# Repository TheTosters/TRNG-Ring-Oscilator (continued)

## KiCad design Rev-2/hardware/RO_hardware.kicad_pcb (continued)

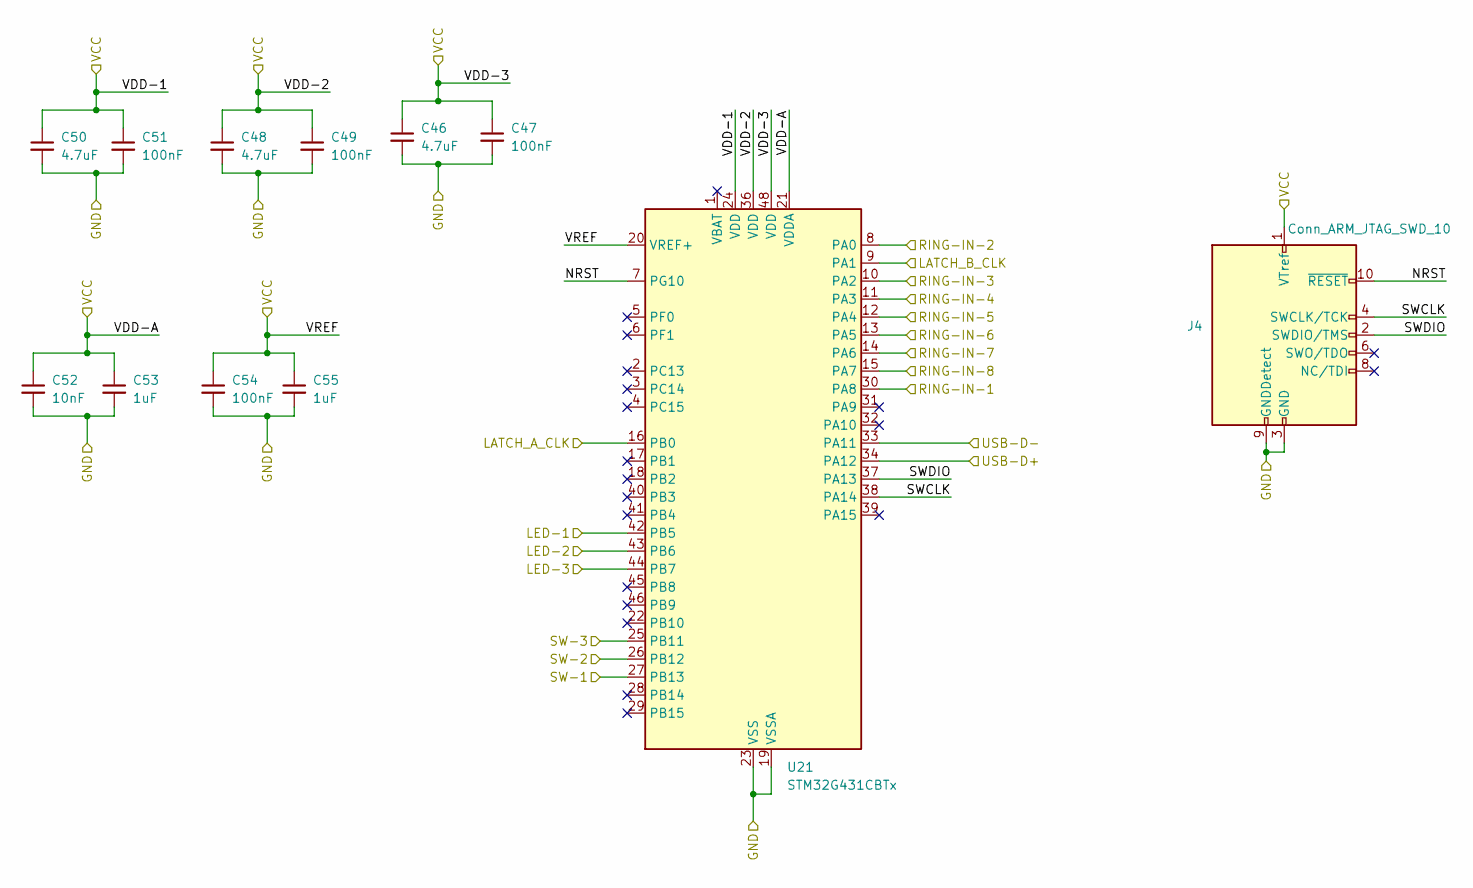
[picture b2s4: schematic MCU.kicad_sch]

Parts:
C46, C48, C50: 4.7uF; C_1206_3216Metric
C47, C49, C51, C54: 100nF; C_1206_3216Metric
C52: 10nF; C_1206_3216Metric
C53, C55: 1uF; C_1206_3216Metric
J4: Conn_ARM_JTAG_SWD_10; Tag-Connect_TC2050-IDC-NL_2x05_P1.27mm_Vertical
U21: STM32G431CBTx; LQFP-48_7x7mm_P0.5mm

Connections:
/CLK_A: U21.16 (PB0); also elsewhere on the board
/CLK_B: U21.9 (PA1); also elsewhere on the board
/D+: U21.34 (PA12); also elsewhere on the board
/D-: U21.33 (PA11); also elsewhere on the board
/MCU/LED-1: U21.42 (PB5); also elsewhere on the board
/MCU/LED-2: U21.43 (PB6); also elsewhere on the board
/MCU/LED-3: U21.44 (PB7); also elsewhere on the board
/MCU/NRST: J4.10 (~RESET), U21.7 (PG10)
/MCU/SW-1: U21.27 (PB13); also elsewhere on the board
/MCU/SW-2: U21.26 (PB12); also elsewhere on the board
/MCU/SW-3: U21.25 (PB11); also elsewhere on the board
/MCU/SWCLK: J4.4 (SWCLK/TCK), U21.38 (PA14)
/MCU/SWDIO: J4.2 (SWDIO/TMS), U21.37 (PA13)
/Q1: U21.12 (PA4); also elsewhere on the board
/Q2: U21.13 (PA5); also elsewhere on the board
/Q3: U21.15 (PA7); also elsewhere on the board
/Q4: U21.14 (PA6); also elsewhere on the board
/TQ1: U21.30 (PA8); also elsewhere on the board
/TQ2: U21.8 (PA0); also elsewhere on the board
/TQ3: U21.11 (PA3); also elsewhere on the board
/TQ4: U21.10 (PA2); also elsewhere on the board
GND: C46.2, C47.2, C48.2, C49.2, C50.2, C51.2, C52.2, C53.2, C54.2, C55.2, J4.3 (GND), J4.5 (GND), J4.9 (GNDDetect), U21.19 (VSSA), U21.23 (VSS), U21.35 (VSS), U21.47 (VSS); also elsewhere on the board
VCC: C46.1, C47.1, C48.1, C49.1, C50.1, C51.1, C52.1, C53.1, C54.1, C55.1, J4.1 (VTref), U21.20 (VREF+), U21.21 (VDDA), U21.24 (VDD), U21.36 (VDD), U21.48 (VDD); also elsewhere on the board

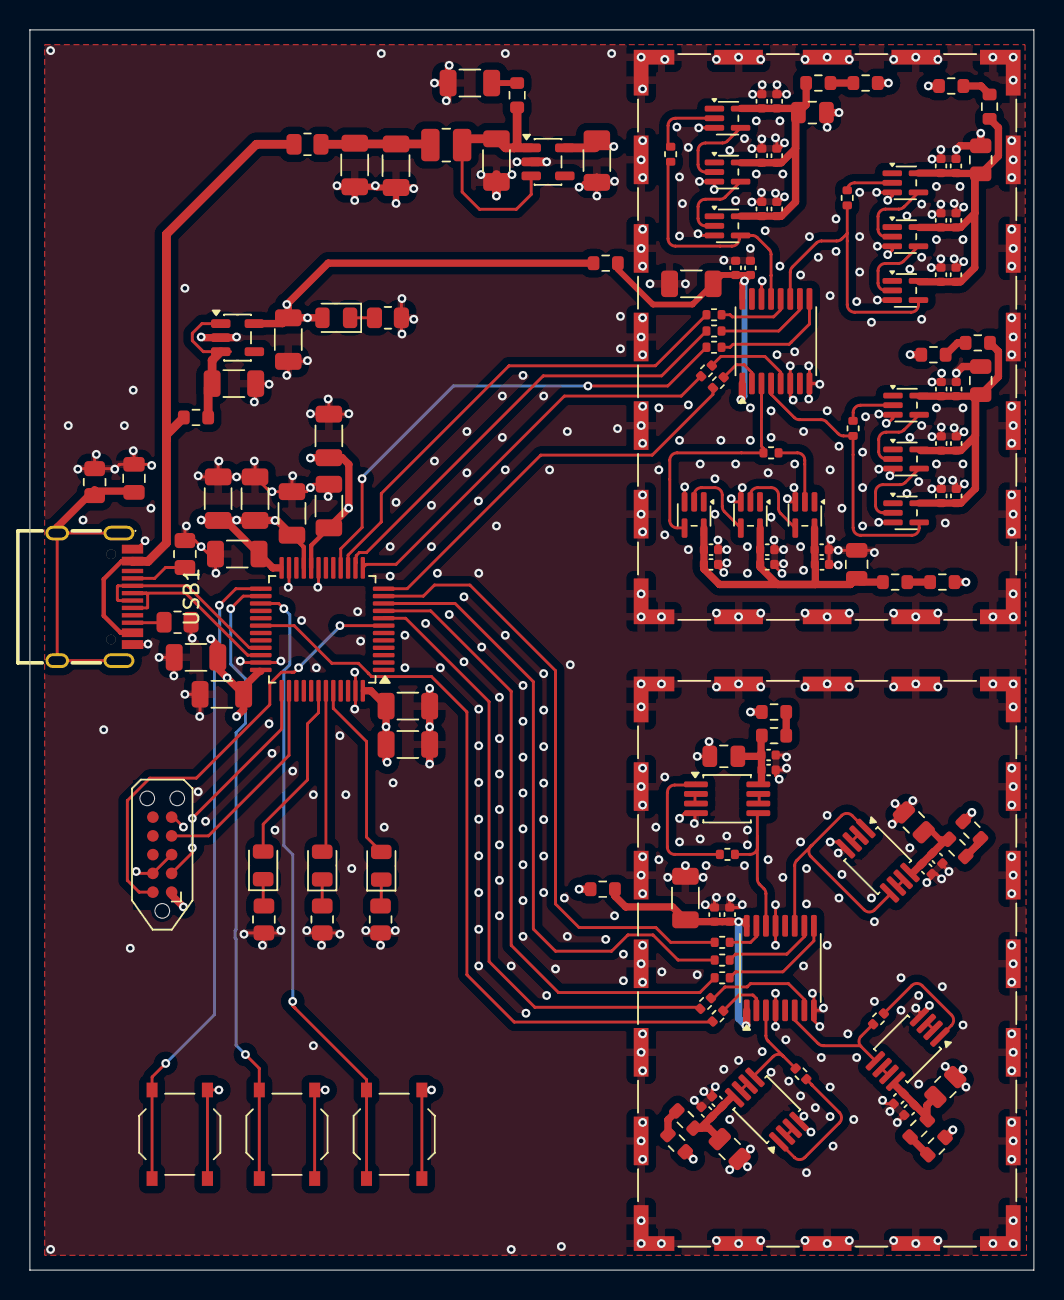
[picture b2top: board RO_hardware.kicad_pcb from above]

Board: 4 copper layers, 68.0 x 84.0 mm, 142 parts (0 on the bottom side), 95 nets.

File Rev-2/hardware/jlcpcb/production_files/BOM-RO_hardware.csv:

Comment,Designator,Footprint,LCSC,Quantity
600@100Mhz,"FB1,FB10,FB11,FB2,FB3,FB4,FB5,FB6,FB7,FB8,FB9",R_0603_1608Metric,C1002,11
10uF,"C2,C58",C_1206_3216Metric,C13585,2
SN74LVC3G04,"U17,U18,U19,U20",MSOP-8_3x3mm_P0.65mm,C139324,4
100nF,"C10,C12,C14,C16,C18,C20,C22,C24,C26,C28,C30,C32,C34,C36,C38,C40,C43,C7",C_0402_1005Metric,C1525,18
4.7nF,"C11,C13,C15,C17,C19,C21,C23,C25,C27,C29,C31,C33,C35,C37,C39,C41,C42,C6",C_0402_1005Metric,C1538,18
10uF,"C44,C45,C56,C57,C59,C60,C8,C9",C_0805_2012Metric,C15850,8
4.7nF,C1,C_0805_2012Metric,C1744,1
1M,R1,R_0805_2012Metric,C17514,1
2.2,R33,R_0805_2012Metric,C17521,1
330,"R22,R23,R24,R7",R_0805_2012Metric,C17630,4
10nF,C52,C_1206_3216Metric,C1846,1
1uF,"C3,C53,C55",C_1206_3216Metric,C1848,3
AP2112K-3.3,"U1,U2",SOT-23-5,C22365427,2
LED,D3,D_0805_2012Metric,C2296,1
LED,"D1,D2",D_0805_2012Metric,C2297,2
4.7,"R25,R26,R27,R28,R29,R30,R31,R32,R34",R_0603_1608Metric,C23164,9
100nF,"C47,C49,C51,C54",C_1206_3216Metric,C24497,4
100,R9,R_0402_1005Metric,C25076,1
120,R6,R_0402_1005Metric,C25079,1
200,R14,R_0402_1005Metric,C25087,1
220,R8,R_0402_1005Metric,C25091,1
22,R2,R_0402_1005Metric,C25092,1
330,R16,R_0402_1005Metric,C25104,1
47,"R10,R11,R12,R13,R15,R17,R18,R19,R20,R21,R5",R_0402_1005Metric,C25120,11
74HC174,"U22,U3",TSSOP-16_4.4x5mm_P0.65mm,C2652842,2
5.1k,"R3,R4",R_0805_2012Metric,C27834,2
4.7uF,"C4,C46,C48,C5,C50,C61,C62,C63,C64",C_1206_3216Metric,C29823,9
SW_Push,"SW1,SW2,SW3",XKBConnection-TS_1187A_B_AB,C318884,3
STM32G431CBTx,U21,LQFP-48_7x7mm_P0.5mm,C529355,1
161N-4WVS11,USB1,USB-C-SMD_HANELECTRICITY_161N-4XVS11,C5440753,1
4.7uH,L2,L_1008_2520Metric,C5832360,1
SN74LVC1G04,"U10,U11,U12,U13,U14,U15,U16,U5,U6,U7,U8,U9",SOT-353_SC-70-5,C8207,12
LED,D4,D_0805_2012Metric,C84256,1
RFShield_OnePiece,J2,Laird_Technologies_BMI-S-205-F_38.10x25.40mm,,1
RFShield_OnePiece,J3,Laird_Technologies_BMI-S-205-F_38.10x25.40mm,,1
Conn_ARM_JTAG_SWD_10,J4,Tag-Connect_TC2050-IDC-NL_2x05_P1.27mm_Vertical,,1

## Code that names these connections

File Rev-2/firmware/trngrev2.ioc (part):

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Mcu.Name=STM32G431C(6-8-B)Tx
Mcu.Package=LQFP48
Mcu.UserName=STM32G431CBTx
PA0.GPIOParameters=GPIO_Label
PA0.GPIO_Label=ring_in2
PA0.Signal=GPIO_Input
PA1.GPIOParameters=GPIO_Speed,GPIO_Label
PA1.GPIO_Label=latch_b
PA1.GPIO_Speed=GPIO_SPEED_FREQ_VERY_HIGH
PA1.Signal=GPIO_Output
PA11.Mode=Device
PA11.Signal=USB_DM
PA12.Mode=Device
PA12.Signal=USB_DP
PA13.Signal=SYS_JTMS-SWDIO
PA14.Signal=SYS_JTCK-SWCLK
PA2.GPIOParameters=GPIO_Label
PA2.GPIO_Label=ring_in3
PA2.Signal=GPIO_Input
PA3.GPIOParameters=GPIO_Label
PA3.GPIO_Label=ring_in4
PA3.Signal=GPIO_Input
PA4.GPIOParameters=GPIO_Label
PA4.GPIO_Label=ring_in5
PA4.Signal=GPIO_Input
PA5.GPIOParameters=GPIO_Label
PA5.GPIO_Label=ring_in6
PA5.Signal=GPIO_Input
PA6.GPIOParameters=GPIO_Label
PA6.GPIO_Label=ring_in7
PA6.Signal=GPIO_Input
PA7.GPIOParameters=GPIO_Label
PA7.GPIO_Label=ring_in8
PA7.Signal=GPIO_Input
PA8.GPIOParameters=GPIO_Label
PA8.GPIO_Label=ring_in1
PA8.Signal=GPIO_Input
PB0.GPIOParameters=GPIO_Speed,GPIO_Label
PB0.GPIO_Label=latch_a
PB0.GPIO_Speed=GPIO_SPEED_FREQ_VERY_HIGH
PB0.Signal=GPIO_Output
PB11.GPIOParameters=GPIO_PuPd,GPIO_Label
PB11.GPIO_Label=sw3
PB11.GPIO_PuPd=GPIO_PULLDOWN
PB11.Signal=GPIO_Input
PB13.GPIOParameters=GPIO_PuPd,GPIO_Label
PB13.GPIO_Label=sw1
PB13.GPIO_PuPd=GPIO_PULLDOWN
PB13.Signal=GPIO_Input
PB5.GPIOParameters=GPIO_Label
PB5.GPIO_Label=led1
PB5.Signal=GPIO_Output
PB6.GPIOParameters=GPIO_Label
PB6.GPIO_Label=led2
PB6.Signal=GPIO_Output
PB7.GPIOParameters=GPIO_Speed,PinState,GPIO_Label
PB7.GPIO_Label=led3
PB7.GPIO_Speed=GPIO_SPEED_FREQ_LOW
PB7.PinState=GPIO_PIN_RESET
PB7.Signal=GPIO_Output
PB8-BOOT0.GPIOParameters=GPIO_PuPd,GPIO_Label
PB8-BOOT0.GPIO_Label=sw2_boot
PB8-BOOT0.GPIO_PuPd=GPIO_PULLDOWN
PB8-BOOT0.Signal=GPIO_Input
RCC.HSE_VALUE=8000000
RCC.SYSCLKFreq_VALUE=168000000
RCC.SYSCLKSource=RCC_SYSCLKSOURCE_PLLCLK
board=custom

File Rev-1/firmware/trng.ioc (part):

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Mcu.Name=STM32F070F6Px
Mcu.Package=TSSOP20
Mcu.UserName=STM32F070F6Px
PA0.Signal=GPIO_Input
PA1.Signal=GPIO_Input
PA11.Mode=Device
PA11.Signal=USB_DM
PA12.Mode=Device
PA12.Signal=USB_DP
PA13.Mode=Serial_Wire
PA13.Signal=SYS_SWDIO
PA14.Mode=Serial_Wire
PA14.Signal=SYS_SWCLK
PA2.Signal=GPIO_Input
PA3.Signal=GPIO_Input
PA4.Signal=GPIO_Input
PA5.GPIOParameters=GPIO_Speed,PinState
PA5.GPIO_Speed=GPIO_SPEED_FREQ_HIGH
PA5.PinState=GPIO_PIN_SET
PA5.Signal=GPIO_Output
PA6.GPIOParameters=PinState,GPIO_PuPd,GPIO_ModeDefaultOutputPP
PA6.GPIO_ModeDefaultOutputPP=GPIO_MODE_OUTPUT_PP
PA6.GPIO_PuPd=GPIO_NOPULL
PA6.PinState=GPIO_PIN_SET
PA6.Signal=GPIO_Output
PA7.Signal=GPIO_Input
PF0-OSC_IN.Mode=HSE-External-Oscillator
PF0-OSC_IN.Signal=RCC_OSC_IN
PF1-OSC_OUT.Mode=HSE-External-Oscillator
PF1-OSC_OUT.Signal=RCC_OSC_OUT
RCC.HSE_VALUE=12000000
RCC.SYSCLKFreq_VALUE=48000000
RCC.SYSCLKSource=RCC_SYSCLKSOURCE_PLLCLK
board=custom
